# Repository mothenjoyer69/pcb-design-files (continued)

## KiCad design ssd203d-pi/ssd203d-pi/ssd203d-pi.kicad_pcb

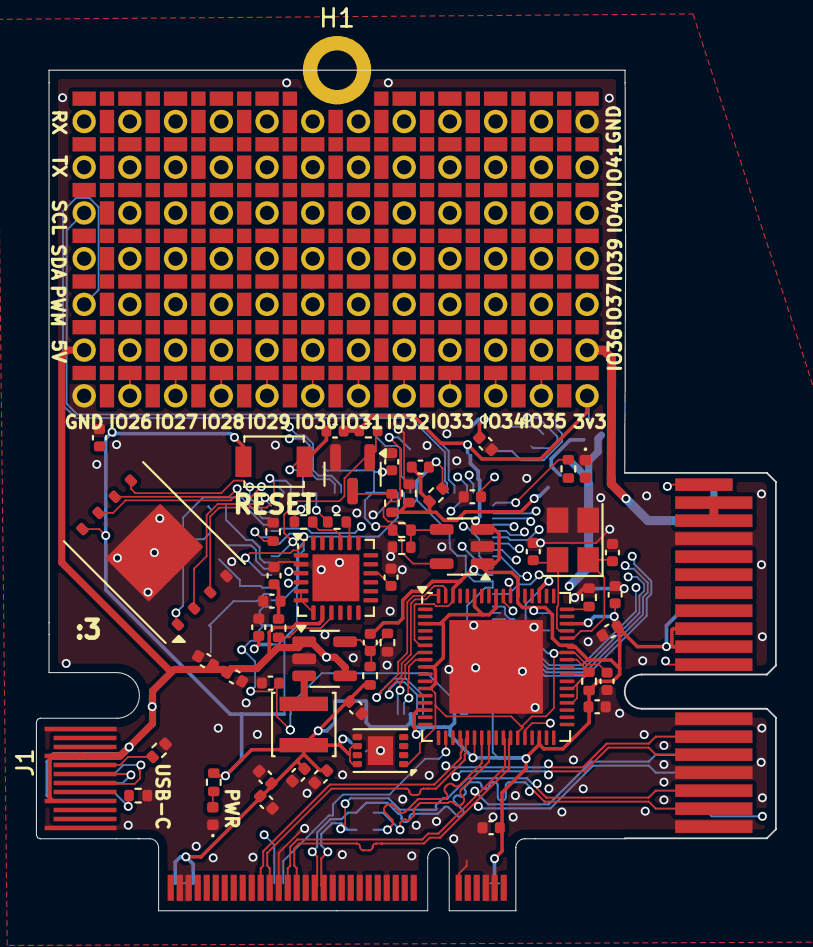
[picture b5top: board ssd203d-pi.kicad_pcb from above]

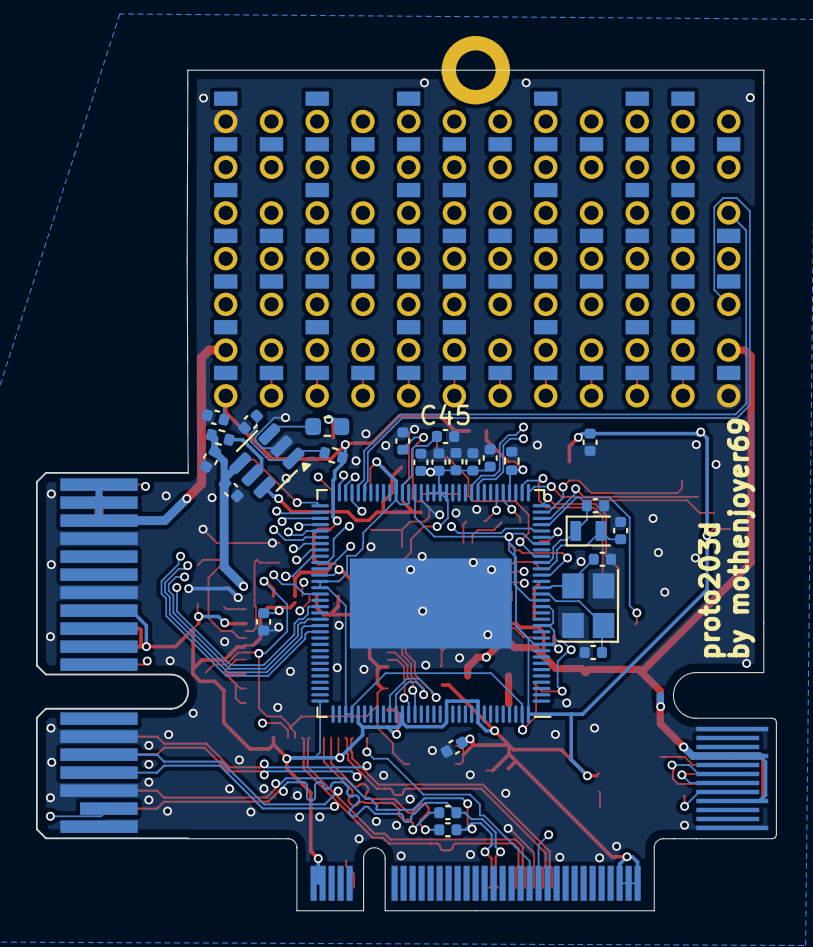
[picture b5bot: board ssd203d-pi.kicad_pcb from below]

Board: 4 copper layers, 41.1 x 46.7 mm, 89 parts (29 on the bottom side), 84 nets.

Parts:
C1, C2, C3, C4, C5, C6, C7, C8, C11, C12, C13, C14, C22, C23, C25, C27, C31, C34, C35, C38, C46: 0.1uF; C_0402_1005Metric
C9: 22uF 10v; C_0402_1005Metric
C10, C29: 1uF; C_0402_1005Metric
C15: 01.uF; C_0402_1005Metric
C16, C17: 15pF; C_0402_1005Metric
C18, C19: 10pF; C_0402_1005Metric
C20, C21, C41, C42: 10uF; C_0402_1005Metric
C24, C26, C30, C33, C37: 22uF; C_0402_1005Metric
C28, C43, C44: 22pF; C_0402_1005Metric
C32: 0.01uF; C_0402_1005Metric
C36: 39pF; C_0402_1005Metric
C39, C40: 100n; C_0402_1005Metric
C45: 470n; C_0402_1005Metric
D1: LED_PWR; LED_0402_1005Metric
D2: LED_USR; LED_0402_1005Metric
H1: M.2 Screw; MountingHole_2.2mm_M2_DIN965_Pad
J1: USB_C_Receptacle_USB2.0_16P; USB_TYPE_C_W_2.0_5
J2: PROTO; PROTO_THT_SMD_4x
J4: Bus_PCI_Express_x1; BUS_PCIexpress_x1
L1: SWPA3015S2R2MT; L_Changjiang_FNR3021S
L2: 2.2uH; L_0603_1608Metric
Q1: 2N7002; SOT-23
R2, R3: 1.5k; R_0402_1005Metric
R4, R10: 5.1k; R_0402_1005Metric
R5, R6: 22r; R_0402_1005Metric
R7, R8: 10k; R_0402_1005Metric
R9, R15, R16, R20: 4.7k; R_0402_1005Metric
R11: 150k; R_0402_1005Metric
R12: 33k; R_0402_1005Metric
R13: 57.6k; R_0402_1005Metric
R14: 240k; R_0402_1005Metric
R17: 50k; R_0402_1005Metric
R18: 100k; R_0402_1005Metric
R19: 300k; R_0402_1005Metric
R21: 6.04k; R_0402_1005Metric
R22: 15k; R_0402_1005Metric
SW1: RESET; SW_SPST_B3U-1000P
U1: QFN-128_EP_12.3x12.3_Pitch0.35mm
U2: W25N02KVZEIR; WSON-8-1EP_8x6mm_P1.27mm_EP3.4x4.3mm
U3: SM8082AAAC; SOT-23-5
U4: CP2104; QFN-24-1EP_4x4mm_P0.5mm_EP2.6x2.6mm
U5: NGFF_B
U6: RS3236-ADJCYF5; SOT-23-5
U7: SY80063ABC; SOT-23-6
U8: TPS784105QWDRBRQ1; SON-8-1EP_3x2mm_P0.5mm_EP1.4x1.6mm
U9: VL805; QFN-68-1EP_8x8mm_P0.4mm_EP5.2x5.2mm
Y1: 24MHz Crystal; Crystal_SMD_3225-4Pin_3.2x2.5mm
Y2: 32.768kHz Crystal; Crystal_SMD_2012-2Pin_2.0x1.2mm
Y3: Crystal_GND23; Crystal_SMD_3225-4Pin_3.2x2.5mm

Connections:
1.05v: C41.2, U8.1 (OUT), U9.3 (VCCA10SSRX34), U9.9 (VDD), U9.12 (VCCA10SSRX34), U9.29 (VDD), U9.45 (VDD), U9.54 (VCCA10SSRX12), U9.60 (VDD), U9.63 (VCCA10SSRX12)
+1V0: C36.1, C37.1, C38.1, L2.2, R17.1, U1.13 (VDD), U1.16 (VDD), U1.28 (VDD), U1.52 (DVDD_DDR), U1.54 (VDD), U1.77 (VDD), U1.78 (VDD), U1.99 (VDD), U1.100 (VDD), U1.127 (VDD)
+12V: J2.19, J4.A2 (+12V), J4.A3 (+12V), J4.B1 (+12V), J4.B2 (+12V), J4.B3 (+12V)
AVDD: C1.1, C2.1, C3.1, C4.1, C5.1, C6.1, C7.1, C8.1, C9.1, C10.1, C15.1, C21.1, C26.1, C27.1, C28.2, C29.2, C42.2, J2.18 (Pin_6), J4.A9 (+3.3V), J4.A10 (+3.3V), J4.B8 (+3.3V), L1.2, R2.2, R11.2, R15.1, R20.2, R22.1, SW1.1, U1.10 (AVDD), U1.17 (AVDD_XTAL), U1.21 (AVDD_RTC), U1.26 (AVDD_NODIE), U1.51 (AVDD_PLL), U1.64 (AVDD_USB), U1.76 (VDDP_1), U1.96 (VDDP_1), U1.101 (AVDD), U1.108 (AVDD_USB), U1.115 (AVDD_HDMITX), U1.120 (AVDD_AUD), U1.128 (AVDD), U2.8 (VCC), U5.2 (3.3V), U5.4 (3.3V), U5.70 (3.3V), U5.72 (3.3V), U5.74 (3.3V), U6.1 (IN), U6.3 (EN), U8.6 (EN), U8.8 (IN), U9.6 (VCCA33SS34), U9.15 (VCCA33SS34), U9.23 (VCCA33PEX), U9.32 (VSUS33), U9.46 (VSUS33), U9.49 (VCCA33SSM), U9.57 (VCCA33SS12), U9.66 (VCCA33SS12)
AVDDIO_DRAM: C11.1, C12.1, C13.1, C14.1, C30.1, C31.1, R13.1, U1.46 (VDDIO_DATA), U1.47 (VDDIO_DATA), U1.48 (VDDIO_DATA), U1.49 (AVDDIO_DRAM), U6.5 (OUT)
GND: C1.2, C2.2, C3.2, C4.2, C5.2, C6.2, C7.2, C8.2, C9.2, C10.2, C11.2, C12.2, C13.2, C14.2, C15.2, C16.1, C17.1, C18.1, C19.1, C20.1, C22.2, C23.2, C24.2, C25.2, C26.2, C27.2, C29.1, C30.2, C31.2, C32.2, C33.2, C34.2, C35.1, C37.2, C38.2, C41.1, C42.1, C43.1, C44.1, C45.2, C46.1, D1.1 (K), D2.1 (K), J1.A1 (GND), J1.A12 (GND), J1.B1 (GND), J1.B12 (GND), J2.7, J2.24 (Pin_12), J4.A4 (GND), J4.A12 (GND), J4.A15 (GND), J4.A18 (GND), J4.B4 (GND), J4.B7 (GND), J4.B13 (GND), J4.B16 (GND), J4.B18 (GND), Q1.2 (S), R4.2, R7.1, R8.2, R10.1, R12.1, R14.2, R18.2, R21.1, U1.50 (AVSSIO_DQ), U1.129 (GND), U2.4 (GND), U2.9 (GND), U3.2 (GND), U4.2 (GND), U4.25 (GND), U5.3 (GND), U5.5 (GND), U5.11 (GND), U5.27 (GND), U5.33 (GND), U5.39 (GND), U5.45 (GND), U5.51 (GND), U5.57 (GND), U5.71 (GND), U5.73 (GND), U6.2 (GND), U7.2 (GND), U8.5 (GND), U8.9 (PAD), U9.69 (GND), Y1.2, Y1.4, Y3.2, Y3.3
GPIO26: J2.8, U1.66 (GPIO26)
GPIO27: J2.9, U1.67 (GPIO27)
GPIO28: J2.10, U1.68 (GPIO28)
GPIO29: J2.11, U1.69 (GPIO29)
GPIO30: J2.12, U1.70 (GPIO30)
GPIO31: J2.13 (Pin_1), U1.71 (GPIO31)
GPIO32: J2.14 (Pin_2), U1.72 (GPIO32)
GPIO33: J2.15 (Pin_3), U1.73 (GPIO33)
GPIO34: J2.16 (Pin_4), U1.74 (GPIO34)
GPIO35: J2.17 (Pin_5), U1.79 (GPIO35)
GPIO37: J2.20 (Pin_8), U1.81 (GPIO37)
GPIO39: J2.21 (Pin_9), U1.83 (GPIO39)
GPIO40: J2.22 (Pin_10), U1.84 (GPIO40)
GPIO41: J2.23 (Pin_11), U1.85 (GPIO41)
I2C0_SCL: J2.3, U1.60 (I2C0_SCL)
I2C0_SDA: J2.4, U1.61 (I2C0_SDA)
LED_USR: R3.2, U1.65 (GPIO25)
M.2_USB_UART_DN-: U4.4 (D-), U9.59 (USB2D1-)
M.2_USB_UART_DP+: U4.3 (D+), U9.58 (USB2D1+)
unnamed: D1.2 (A), R2.1
unnamed: D2.2 (A), R3.1
unnamed: J1.A5 (CC1), R10.2
unnamed: J1.B5 (CC2), R4.1
unnamed: J4.A1 (~PRSNT1), J4.B17 (~PRSNT2)
unnamed: Q1.3 (D), R19.2
unnamed: C46.2, U1.75 (AVDD1P2)
unnamed: C45.1, U1.53 (DVDD_DDR_RX)
unnamed: R7.2, U1.27 (GND_EFUSE)
unnamed: C17.2, U1.18 (XTAL_IN), Y1.1
unnamed: C18.2, U1.22 (XTAL_IN_32K), Y2.2
unnamed: C16.2, U1.19 (XTAL_OUT), Y1.3
unnamed: C19.2, U1.23 (XTAL_OUT_32K), Y2.1
unnamed: C28.1, R11.1, R12.2, U3.5 (FB)
unnamed: L1.1, U3.3 (LX)
unnamed: C22.1, C23.1, R9.1, U4.5 (VIO), U4.6 (VDD), U4.7 (REGIN)
unnamed: C20.2, U4.16 (VPP)
unnamed: R9.2, U4.9 (~RST)
unnamed: C32.1, R13.2, R14.1, U6.4 (BP/FP)
unnamed: C35.2, R15.2, U7.1 (EN)
unnamed: C36.2, R17.2, R18.1, R19.1, U7.6 (FB)
unnamed: L2.1, U7.3 (LX)
unnamed: R16.1, U7.5 (PG)
unnamed: R21.2, U9.51 (TESTEN)
unnamed: C44.2, U9.47 (XI), Y3.1
unnamed: C43.2, U9.48 (XO), Y3.4
unnamed: R22.2, U9.38 (~USBHPE4), U9.40 (~USBHPE3), U9.42 (~USBHPE2), U9.44 (~USBHPE1)
PE_CLK_N: J4.A14 (REFCLK-), U5.53 (REFCLK-), U9.22 (PE_CLKN)
PE_CLK_P: J4.A13 (REFCLK+), U5.55 (REFCLK+), U9.21 (PE_CLKP)
PE_CLK_nREQ: U5.52 (~CLKREQ), U9.30 (~PE_CLKREQ)
PE_RX_C_N: C40.2, U9.25 (PE_TXN)
PE_RX_C_P: C39.2, U9.24 (PE_TXP)
PE_RX_N: C40.1, J4.A17 (PERn0), U5.43 (PER0+/B-)
PE_RX_P: C39.1, J4.A16 (PERp0), U5.41 (PER0-/B+)
PE_TX_N: J4.B15 (PETn0), U5.47 (PET0-/A-), U9.28 (PE_RXN)
PE_TX_P: J4.B14 (PETp0), U5.49 (PET0+/A+), U9.27 (PE_RXP)
PE_nRST: J4.A11 (~PERST), U5.50 (~PERST), U9.19 (~PE_RST)
PWM0: J2.5, U1.59 (PWM0)
RESET: C21.2, R8.1, SW1.2, U1.36 (PM_RESET)
SAR_GPIO1: Q1.1 (G), R20.1, U1.24 (SAR_GPIO1)
SPI_CLK: U1.30 (PM_SPI_CK), U2.6 (CLK)
SPI_CS: U1.29 (PM_SPI_CZ), U2.1 (CS)
SPI_HLD: U1.33 (PM_SPI_HLD), U2.7 (HOLD/IO3)
SPI_MISO: U1.32 (PM_SPI_DO), U2.2 (DO/IO1)
SPI_MOSI: U1.31 (PM_SPI_DI), U2.5 (DI/IO0)
SPI_WP: U1.34 (PM_SPI_WPZ), U2.3 (WP/IO2)
UART0_RXD: R6.1, U1.37 (PM_UART_RX)
UART0_TXD: R5.1, U1.38 (PM_UART_TX)
UART1_RX: J2.1, U1.42 (UART1_TX)
UART1_TX: J2.2, U1.41 (UART1_RX)
USB1_DN-: J1.A7 (D-), J1.B7 (D-), U1.63 (DM_P1)
USB1_DP+: J1.A6 (D+), J1.B6 (D+), U1.62 (DP_P1)
USB2_DN-: U1.107 (DM_P2), U9.68 (USB2D2-)
USB2_DP+: U1.106 (DP_P2), U9.67 (USB2D2+)
USB3_DN-: U1.109 (DM_P3), U9.8 (USB2D3-)
USB3_DP+: U1.110 (DP_P3), U9.7 (USB2D3+)
USB_UART_RX: R5.2, U4.20 (RXD)
USB_UART_TX: R6.2, U4.21 (TXD)
VBUS: C24.1, C25.1, C33.1, C34.1, J1.A4 (VBUS), J1.A9 (VBUS), J1.B4 (VBUS), J1.B9 (VBUS), J2.6, R16.2, U3.1 (EN), U3.4 (IN), U4.8 (VBUS), U7.4 (IN)

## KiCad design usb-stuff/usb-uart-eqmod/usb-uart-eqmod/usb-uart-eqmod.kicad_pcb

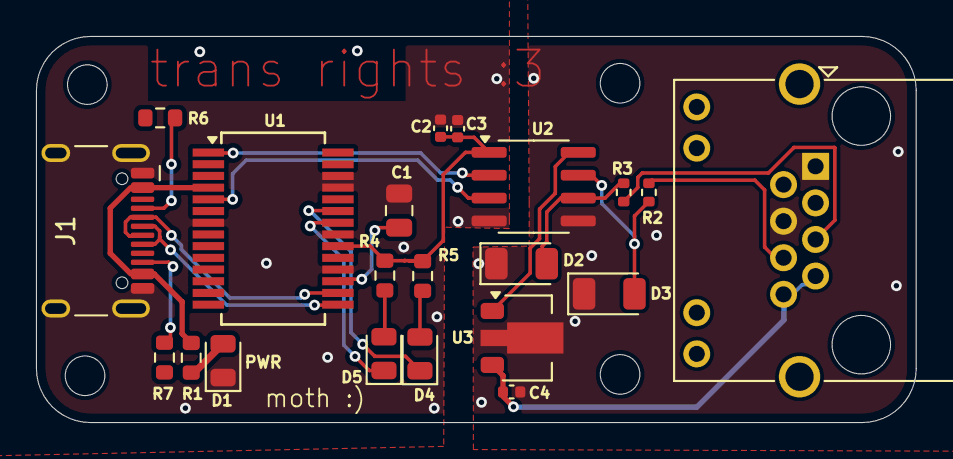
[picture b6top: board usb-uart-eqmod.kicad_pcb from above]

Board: 2 copper layers, 48.9 x 21.5 mm, 25 parts (0 on the bottom side), 22 nets.

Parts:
C1: 100nF; C_0805_2012Metric
C2, C3: 100nF; C_0402_1005Metric
C4: 0.33uF; C_0402_1005Metric
D1: PWR; LED_0805_2012Metric
D2: 4V7; D_1206_3216Metric
D3: 5V1; D_1206_3216Metric
D4: RX; LED_0805_2012Metric
D5: TX; LED_0805_2012Metric
H1, H2, H3, H4: MountingHole; MountingHole_2.2mm_M2
J1: USB_C_Receptacle_USB2.0_14P; USB_C_Receptacle_HCTL_HC-TYPE-C-16P-01A
J2: RJ45; RJ45_Amphenol_RJHSE538X
R1, R4, R5: 270r; R_0603_1608Metric
R2, R3: 200r; R_0402_1005Metric
R6, R7: 5.6k; R_0603_1608Metric
U1: FT232RL; SSOP-28_5.3x10.2mm_P0.65mm
U2: ADuM1200AR; SOIC-8_3.9x4.9mm_P1.27mm
U3: L78L05_SOT89; SOT-89-3

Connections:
GND: R6.2, R7.2
GND_A: C1.1, C2.1, C3.1, D1.1 (K), J1.A1 (GND), J1.A12 (GND), J1.B1 (GND), J1.B12 (GND), J1.S1 (SHIELD), U1.7 (GND), U1.18 (GND), U1.21 (GND), U1.25 (AGND), U1.26 (TEST), U2.4 (GND1)
GND_B: C4.1, D2.1 (K), D3.1 (K), J2.1, J2.4, U2.5 (GND2), U3.2 (GND)
unnamed: D1.2 (A), R1.1
unnamed: D2.2 (A), R2.1, U2.6 (VOB)
unnamed: D3.2 (A), R3.1, U2.7 (VOA)
unnamed: D4.2 (A), R4.1
unnamed: D4.1 (K), U1.22 (CBUS1)
unnamed: D5.2 (A), R5.1
unnamed: D5.1 (K), U1.23 (CBUS0)
unnamed: J1.A5 (CC1), R6.1
unnamed: J1.B5 (CC2), R7.1
unnamed: J2.5, R2.2
unnamed: J2.6, R3.2
unnamed: C1.2, U1.17 (3V3OUT)
unnamed: U1.5 (RXD), U2.3 (VIB)
unnamed: U1.1 (TXD), U2.2 (VIA)
unnamed: J1.A6 (D+), J1.B6 (D+), U1.15 (USBD+)
unnamed: J1.A7 (D-), J1.B7 (D-), U1.16 (USBD-)
unnamed: C2.2, C3.2, J1.A4 (VBUS), J1.A9 (VBUS), J1.B4 (VBUS), J1.B9 (VBUS), R1.2, R4.2, R5.2, U1.4 (VCCIO), U1.20 (VCC), U2.1 (VDD1)
unnamed: U2.8 (VDD2), U3.1 (OUT)
unnamed: C4.2, J2.7, J2.8, U3.3 (IN)

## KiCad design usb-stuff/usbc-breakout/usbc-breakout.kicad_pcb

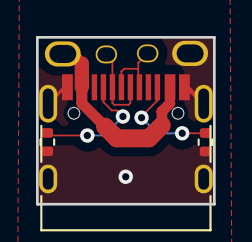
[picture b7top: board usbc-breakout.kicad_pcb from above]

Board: 2 copper layers, 9.8 x 9.3 mm, 7 parts (0 on the bottom side), 6 nets.

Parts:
J1: USB_C_Receptacle_USB2.0; USB_C_Receptacle_HRO_TYPE-C-31-M-12
J2, J3, J4, J5: Conn_01x01_Pin; Pin_D0.7mm_L6.5mm_W1.8mm_FlatFork
R1, R2: TBD; R_0402_1005Metric

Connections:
/USBN-: J1.A7 (D-), J1.B7 (D-), J2.1
/USBP+: J1.A6 (D+), J1.B6 (D+), J4.1
/VBUS: J1.A4 (VBUS), J1.A9 (VBUS), J1.B4 (VBUS), J1.B9 (VBUS), J3.1
GND: J1.A1 (GND), J1.A12 (GND), J1.B1 (GND), J1.B12 (GND), J1.S1 (SHIELD), J5.1, R1.2, R2.2
unnamed: J1.A5 (CC1), R1.1
unnamed: J1.B5 (CC2), R2.1
